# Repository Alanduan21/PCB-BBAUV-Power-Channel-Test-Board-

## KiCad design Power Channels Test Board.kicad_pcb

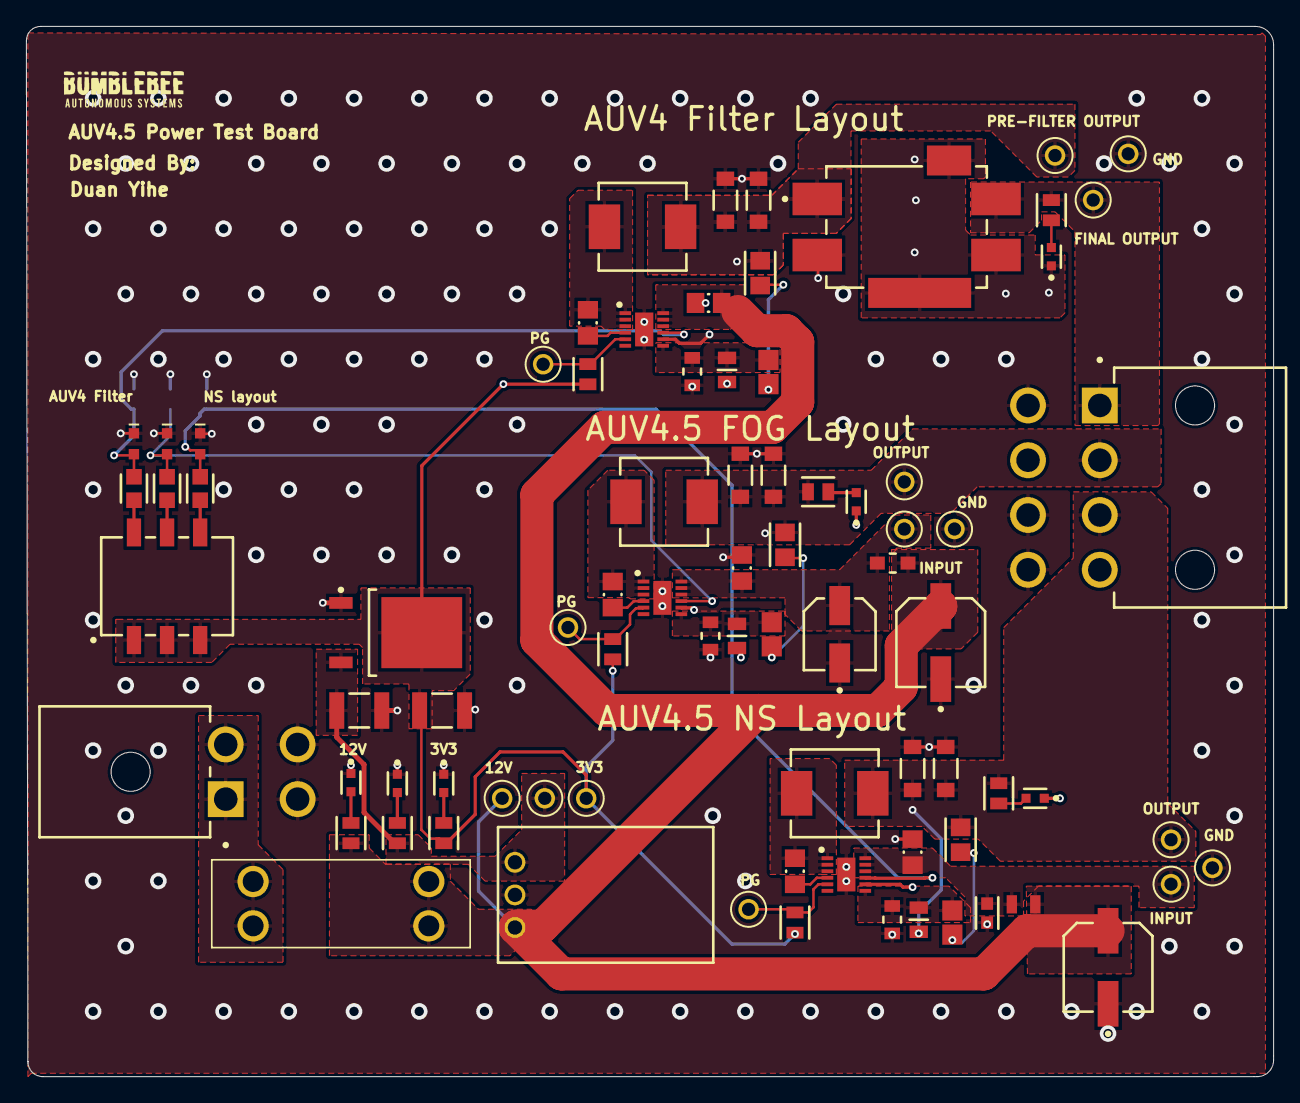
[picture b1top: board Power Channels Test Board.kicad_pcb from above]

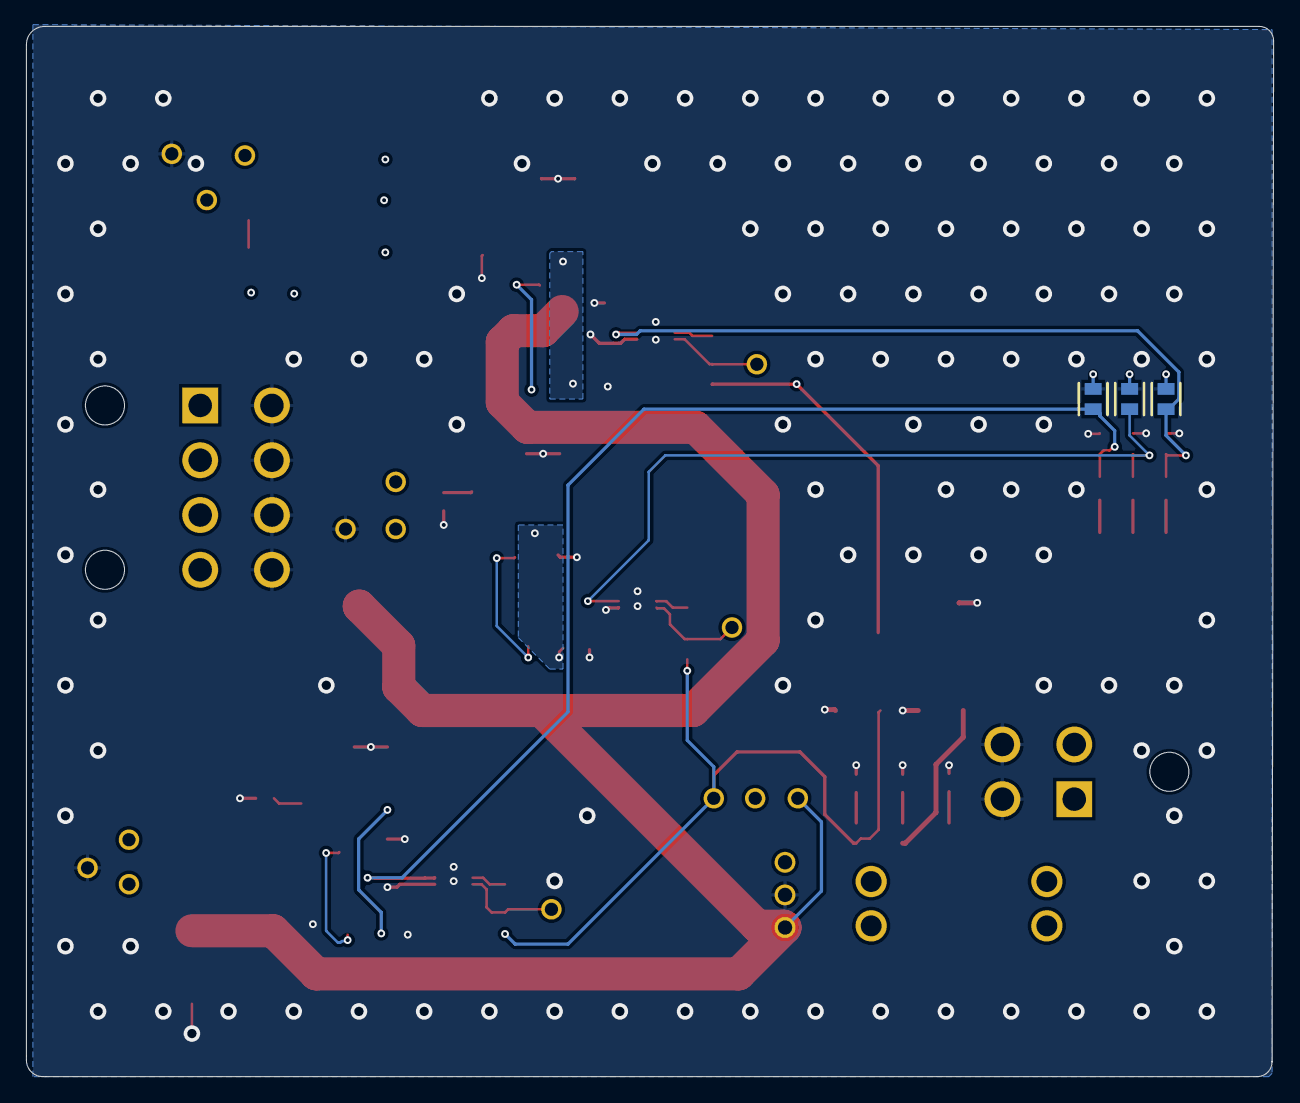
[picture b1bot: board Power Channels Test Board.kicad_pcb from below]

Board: 4 copper layers, 95.6 x 80.5 mm, 84 parts (3 on the bottom side), 39 nets.

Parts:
1: OKI-78SR-5/1.5-W36H-C (RA); (RA) MURA-OKI-78SR-3
C1, C2: 10uF 1012; CAPC3225X22X30ML30
C3: 20SVPF120M; FP-OS-CON-SMT-C6-MFG
C4: 22uF; FP-CL10-IPC_B
C5: 120uF; FP-OS-CON-SMT-C6-MFG
C6: 39uF; FP-OS-CON-SMT-B6-MFG
C7, C8, C9, C10, C11, C12: 33uF 1206; FP-C3216-160-0_2-MFG
C30, C32, C35, C37, C40, C42: 100n 0805; CAPC0805(2012)145_M
C31, C36, C41: 33pF 0805; CAPC2013X94X50ML20T25
D1, D2, D4, D8, D10, D11: LSM0603453V; FP-LSM0603453V-MFG
D3, D5, D9: Yellow 0603; WL-SMCW_0603_150060xx75000
F1: 3557-2; FUSE_3557-2
FL2: BNX026H01L; FP-BNX02-MFG
J1: 39-30-0040; FP-39-30-0040-MFG
J2: 39-30-0080; FP-39-30-0080-MFG
L1: 1uH; WE-PMI_0805_L2W1.2H0.5
L3: 1.5uH; FP-LQM21PN_C0-MFG
L6, L7, L8: 4.7uH; FP-IHLP-2525CZ-FP_2_413x3-MFG
R1, R2, R4, R7, R11, R76, R78, R83, R84, R85, R90, R91: 10k 0805; FP-CRGCQ0805-IPC_C
R3, R5, R6: 3.3k 0805; FP-TFCR0805-MFG
R12, R13, R14: MCU0805MD1003DP500; FP-MCU0805-IPC_B
R72, R79, R86: 1k 0805; FP-TFCR0805-IPC_A
R75, R82, R89: 19.1k 0805; FP-AC0805-MFG
SW1: A6SN-3101; FP-A6SN-3101-MFG
TP1, TP2, TP3, TP4, TP5, TP6, TP7, TP8, TP9, TP10, TP11, TP12, TP14, TP15, TP17: 5001; FP-5001-MFG
U1: LD1086DT33TR; TO-252_L
U7, U8, U9: LMR51450FNDRRR; SON50P300X300X80-13N-D

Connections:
5_EN_1: D9.2, R3.1, R83.2, U8.9
5_EN_2: D3.2, R5.1, R90.2, U9.9
5_EN_3: D5.2, R6.1, R76.2, U7.9
5_NS_OUT: C7.1, C8.1, J2.3, L6.2, R7.2, R13.2, R72.2, TP8.1
5_PG_1: R84.1, TP10.1, U8.5
5_PG_2: R91.1, TP14.1, U9.5
5_PG_3: R78.1, TP11.1, U7.5
5_PSB4_5_OUT: C11.1, C12.1, J2.2, L8.2, R11.2, R12.2, R86.2, TP15.1
5_PSB4_OUT: FL2.2, J2.1, R85.2, TP12.1
+3V3: C2.2, R1.1, R78.2, R84.2, R91.2, SW1.1, SW1.2, SW1.3, TP6.1, U1.4
+5: 1.3, C1.2, R4.1, TP5.1, U1.3
+12: 1.1, C3.2, C5.2, C37.2, F1.2_1, F1.2_2, L1.1, L3.1, R2.1, TP1.1, U8.10, U8.11, U8.12
+12_IN: F1.1_1, F1.1_2, J1.1, J1.2
BOOT_NS: C30.2, U7.4
BOOT_PSB4: C35.2, U8.4
BOOT_PSB4_5: C40.2, U9.4
FB_NS: C31.1, R13.1, R75.2, U7.7
FB_PSB4: C36.1, R14.1, R82.2, U8.7
FB_PSB4_5: C41.1, R12.1, R89.2, U9.7
GND: 1.2, C1.1, C2.1, C3.1, C4.2, C5.1, C6.1, C7.2, C8.2, C9.2, C10.2, C11.2, C12.2, C32.1, C37.1, C42.1, D1.1, D2.1, D3.1, D4.1, D5.1, D8.1, D9.1, D11.1, FL2.3, J1.3, J1.4, J2.5, J2.6, J2.7, J2.8, R75.1, R76.1, R82.1, R83.1, R89.1, R90.1, TP2.1, TP4.1, TP7.1, U1.1, U7.8, U7.13, U8.8, U8.13, U9.8, U9.13
GND_5V_FILTERED: D10.1, FL2.4
NetC31_2: C31.2, R72.1
NetC36_2: C36.2, R79.1
NetC41_2: C41.2, R86.1
NetD1_2: D1.2, R1.2
NetD2_2: D2.2, R2.2
NetD4_2: D4.2, R7.1
NetD8_2: D8.2, R4.2
NetD10_2: D10.2, R85.1
NetD11_2: D11.2, R11.1
NetR3_2: R3.2, SW1.6
NetR5_2: R5.2, SW1.5
NetR6_2: R6.2, SW1.4
SW_NS: C30.1, L6.1, U7.1, U7.2, U7.3
SW_PSB4: C35.1, L7.1, U8.1, U8.2, U8.3
SW_PSB4_5: C40.1, L8.1, U9.1, U9.2, U9.3
VIN_NS: C4.1, C32.2, L1.2, TP3.1, U7.10, U7.11, U7.12
VIN_PSB_4_5: C6.2, C42.2, L3.2, TP9.1, U9.10, U9.11, U9.12
VOUT_PSB4: C9.1, C10.1, FL2.1, L7.2, R14.2, R79.2, TP17.1
